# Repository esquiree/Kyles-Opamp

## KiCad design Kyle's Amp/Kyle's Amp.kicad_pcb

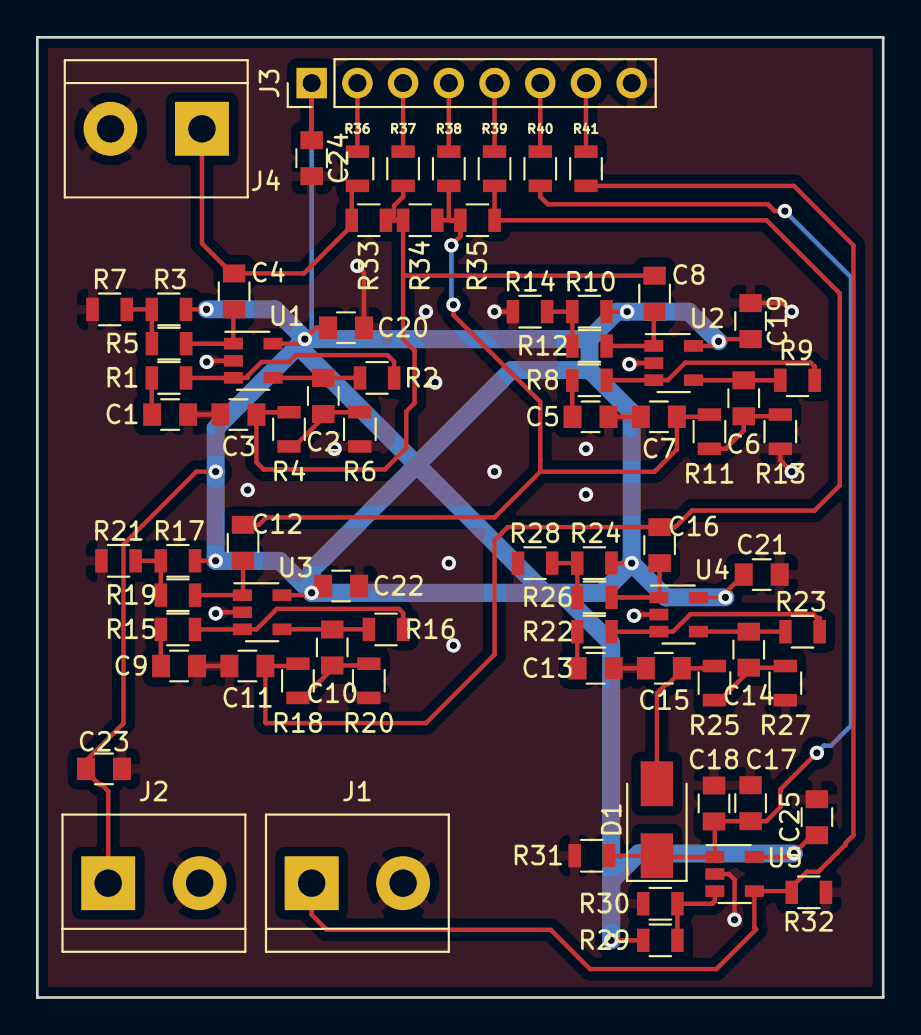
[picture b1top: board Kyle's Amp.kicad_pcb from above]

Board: 2 copper layers, 47.0 x 53.3 mm, 76 parts (0 on the bottom side), 40 nets.

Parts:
C1, C5, C9, C13: 1uF; C_0805
C2, C3, C6, C7, C10, C11, C14, C15, C17, C19, C20, C21, C22: 1nF; C_0805
C4, C8, C12, C16, C18, C23, C24, C25: 0.1uF; C_0805
D1: D; D_SMA
J1, J2, J4: Conn_01x02; TerminalBlock_bornier-2_P5.08mm
J3: Conn_01x06; Pin_Header_Straight_1x08_Pitch2.54mm
R1, R8, R15, R22, R36, R37, R38, R39, R40, R41: 1k; R_0805
R2, R3, R7, R9, R10, R14, R16, R17, R21, R23, R24, R28: 10k; R_0805
R4, R11, R18, R25: 5k; R_0805
R5, R12, R19, R26: 50k; R_0805
R6, R13, R20, R27: 5.6k; R_0805
R29: 70k; R_0805
R30, R31, R32: 100k; R_0805
R33, R34, R35: 0; R_0805
U1, U2, U3, U4, U5: LMV321; SOT-23-5

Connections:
ENVOLPE: C17.2, C18.2, D1.1, R31.2, R40.2, U5.1
GND: C1.2, C3.1, C5.2, C7.1, C9.2, C11.1, C13.2, C15.1, C17.1, C18.1, C19.1, C20.1, C21.1, C22.1, C23.2, C24.2, C25.2, J1.2, J2.2, J3.8, J4.2, R6.1, R7.1, R13.1, R14.1, R20.1, R21.1, R27.1, R28.1, R30.1, R31.1, R32.1, U1.2, U2.2, U3.2, U4.2, U5.2
GPIO: J1.1, R32.2, R41.2, U5.4
INPUT1: C4.2, J4.1, R33.2, R36.2
INPUT2: C3.2, C8.2, R4.2, R33.1, R34.2, R37.2
INPUT3: C7.2, C12.2, R11.2, R34.1, R35.2, R38.2
INPUT4: C11.2, C16.2, R18.2, R35.1, R39.2
unnamed: C1.1, R1.2
unnamed: C2.1, R4.1, R6.2
unnamed: C2.2, R2.1, U1.4
unnamed: C4.1, R5.1, U1.1
unnamed: C5.1, R8.2
unnamed: C6.1, R11.1, R13.2
unnamed: C6.2, R9.1, U2.4
unnamed: C8.1, R12.1, U2.1
unnamed: C9.1, R15.2
unnamed: C10.1, R18.1, R20.2
unnamed: C10.2, R16.1, U3.4
unnamed: C12.1, R19.1, U3.1
unnamed: C13.1, R22.2
unnamed: C14.1, R25.1, R27.2
unnamed: C14.2, R23.1, U4.4
unnamed: C16.1, R26.1, U4.1
unnamed: J3.2, R36.1
unnamed: J3.3, R37.1
unnamed: J3.4, R38.1
unnamed: J3.5, R39.1
unnamed: J3.6, R40.1
unnamed: J3.7, R41.1
unnamed: R1.1, R2.2, U1.3
unnamed: R3.1, R5.2, R7.2
unnamed: R8.1, R9.2, U2.3
unnamed: R10.1, R12.2, R14.2
unnamed: R15.1, R16.2, U3.3
unnamed: R17.1, R19.2, R21.2
unnamed: R22.1, R23.2, U4.3
unnamed: R24.1, R26.2, R28.2
unnamed: R29.1, R30.2, U5.3
OUTPUT: C15.2, D1.2, R25.2
VCC: C19.2, C20.2, C21.2, C22.2, C23.1, C24.1, C25.1, J2.1, J3.1, R3.2, R10.2, R17.2, R24.2, R29.2, U1.5, U2.5, U3.5, U4.5, U5.5
